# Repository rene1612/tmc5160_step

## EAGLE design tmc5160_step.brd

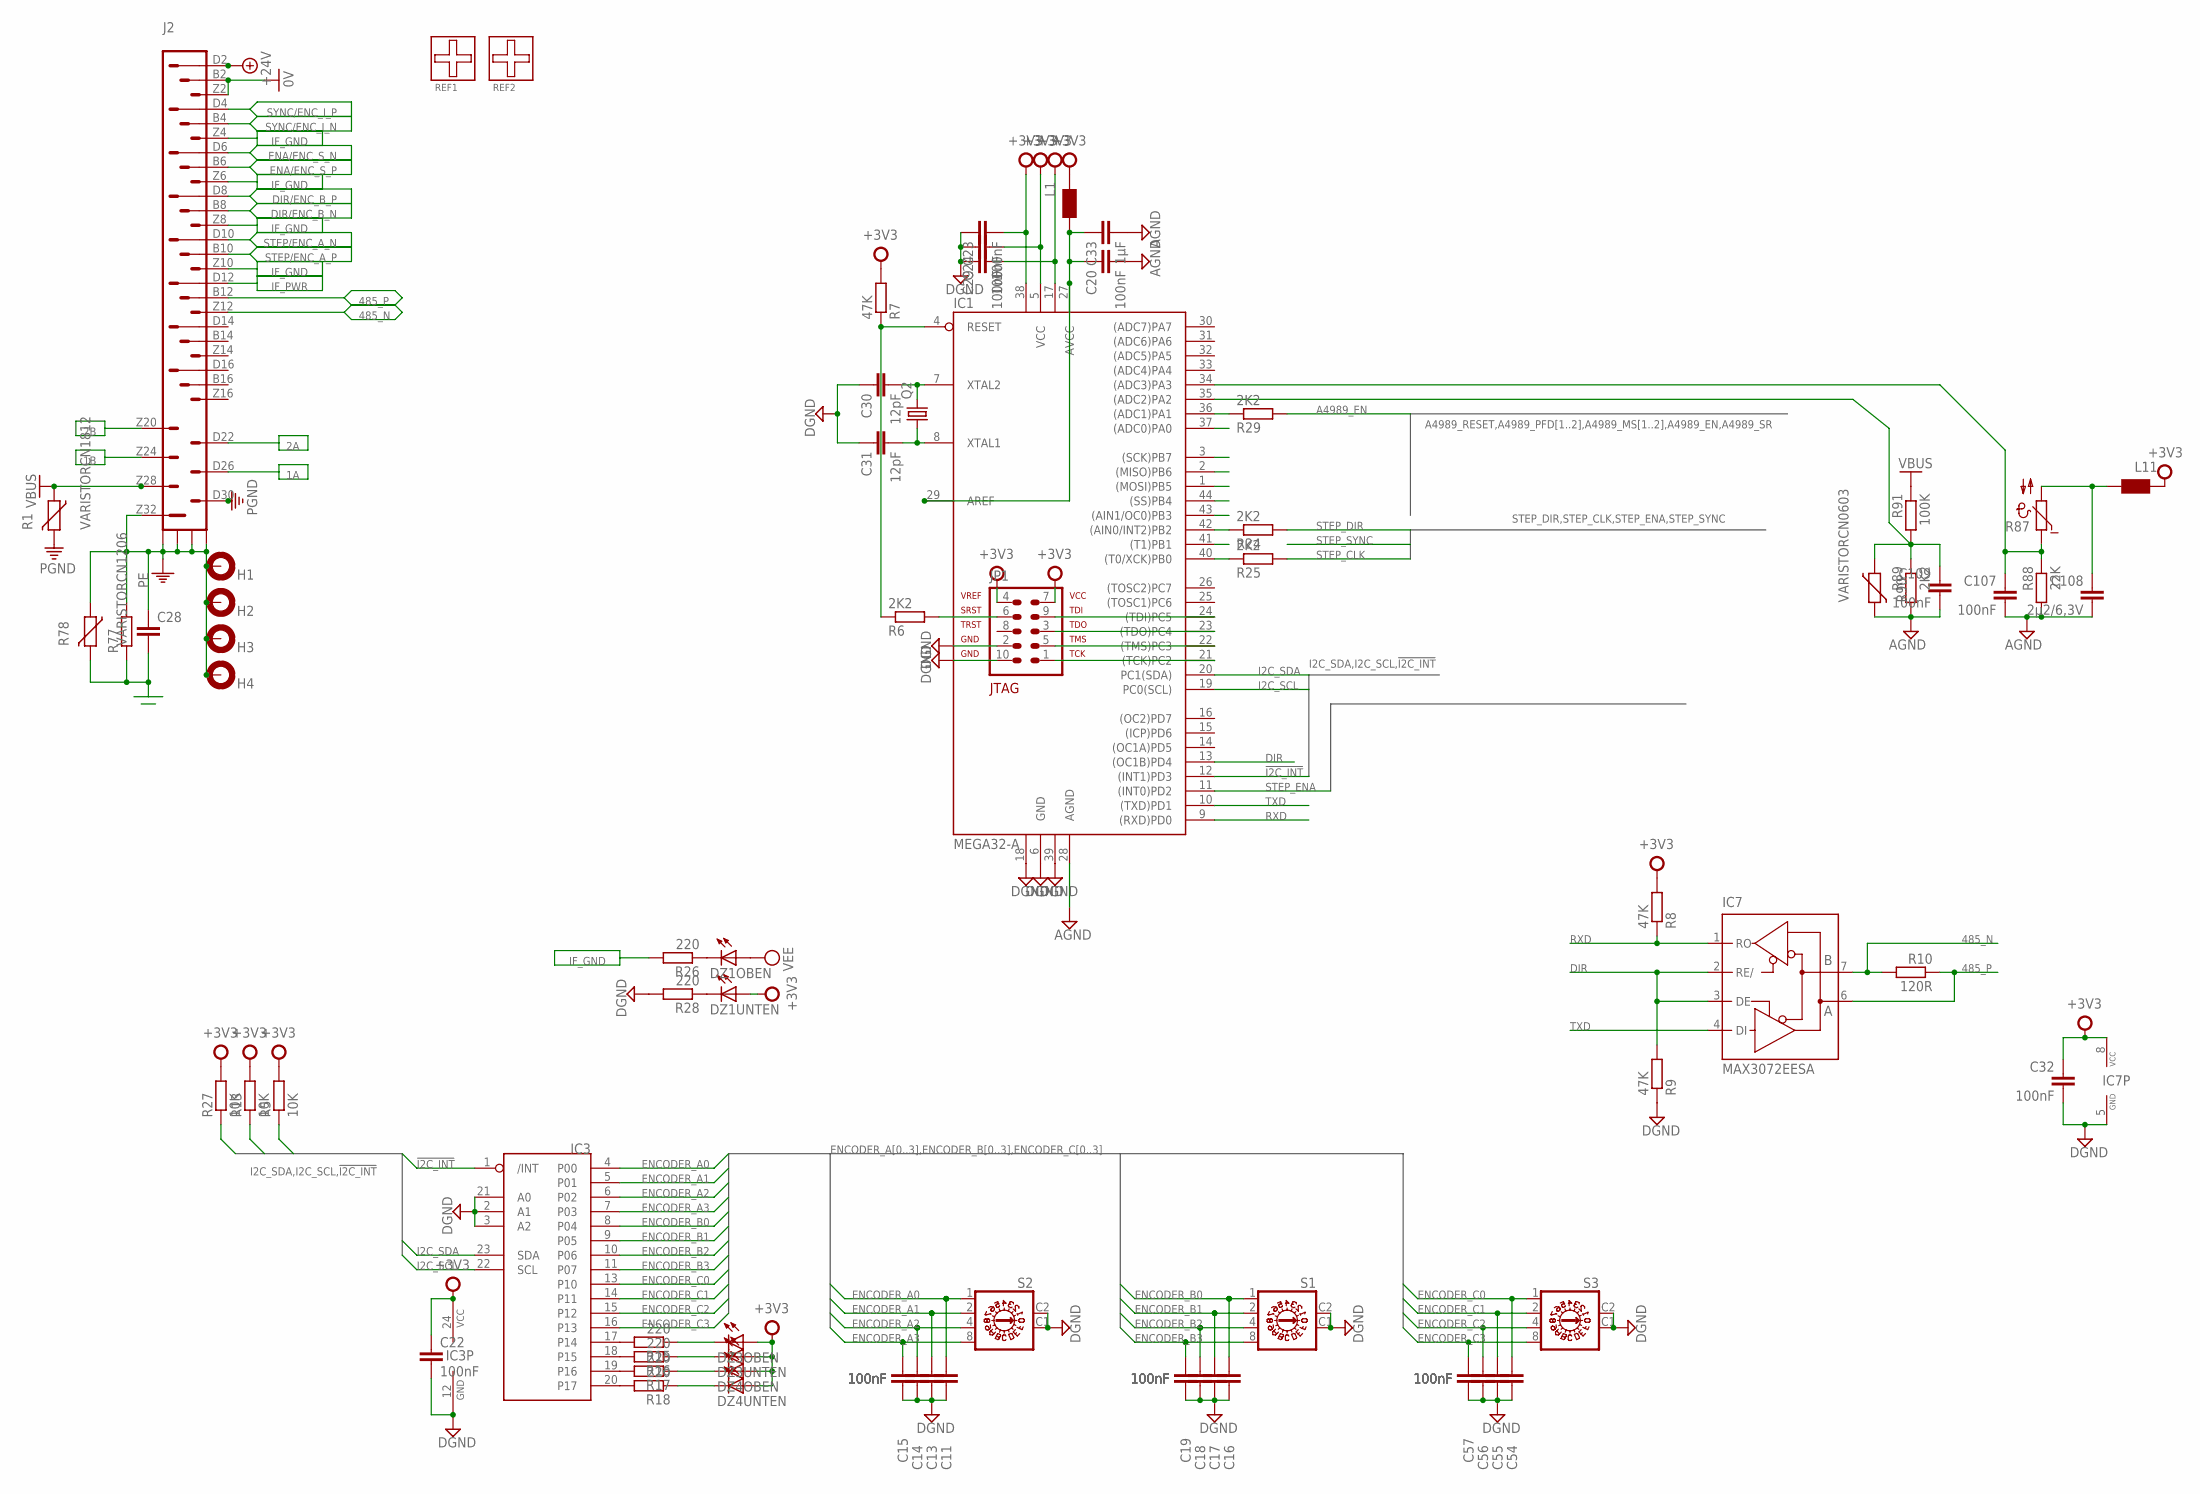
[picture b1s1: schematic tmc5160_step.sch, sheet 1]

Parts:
C11, C13, C14, C15, C16, C17, C18, C19, C20, C22, C23, C24, C29, C32, C54, C55, C56, C57, C107, C109: 100nF; C0603
C28: C-EUC1812; C1812
C30, C31: 12pF; C0603
C33: 1µF; C0603
C108: 2µ2/6,3V; C0603
DZ1, DZ3, DZ4: 18011801; 1801
H1, H2, H3, H4: MOUNT-PAD-ROUND2,5; 2,5-PAD
IC1: MEGA32-A; TQFP44
IC3: PCF8575; MSSOP24
IC7: MAX3072EESA; SO08
J2: H7/24L; H7/24L_EK_FP
JP1: AVR-JTAG-10-R; AVR-JTAG-10R
L1, L11: WE-CBF_0805; 0805
Q2: CRYSTALHC49S; HC49/S
R1: VARISTORCN1812; CT/CN1812
R5, R13, R27: 10K; R0603
R6, R24, R25, R29, R89: 2K2; R0603
R7, R8, R9: 47K; R0603
R10: 120R; R0603
R15, R16, R17, R18, R26, R28: 220; R0603
R77: R-EU_R1206; R1206
R78: VARISTORCN1206; CT/CN1206
R87: NTC642-6; P642
R88: 22K; R0603
R90: VARISTORCN0603; CT/CN0603
R91: 100K; R0603
REF1, REF2: FIDUCIAL_REF-DRUCK; REF-DRUCK
S1, S2, S3: COPAL_HEX

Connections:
0V: J2.B2, J2.Z2; also elsewhere on the board
1A: J2.D26; also elsewhere on the board
1B: J2.Z24; also elsewhere on the board
2A: J2.D22; also elsewhere on the board
2B: J2.Z20; also elsewhere on the board
485_N: IC7.7 (B), J2.Z12, R10.2
485_P: IC7.6 (A), J2.B12, R10.1
!I2C_INT: IC1.12 ((INT1)PD3), IC3.1 (/INT), R5.1
+3V3: C22.1, C23.2, C24.2, C29.2, C32.1, DZ1.UA (A), DZ3.OA (A), DZ3.UA (A), DZ4.OA (A), DZ4.UA (A), IC1.5 (VCC), IC1.17 (VCC1), IC1.38 (VCC2), IC3.24 (VCC), IC7.8 (VCC), JP1.4, JP1.7, L1.1, L11.1, R5.2, R7.2, R8.2, R13.2, R27.2; also elsewhere on the board
+24V: J2.D2; also elsewhere on the board
A4989_EN: R29.2; also elsewhere on the board
AGND: C20.2, C33.2, C107.2, C108.2, C109.2, IC1.28 (AGND), R88.2, R89.2, R90.2; also elsewhere on the board
DGND: C11.1, C13.1, C14.1, C15.1, C16.1, C17.1, C18.1, C19.1, C22.2, C23.1, C24.1, C29.1, C30.1, C31.1, C32.2, C54.1, C55.1, C56.1, C57.1, IC1.6 (GND), IC1.18 (GND1), IC1.39 (GND2), IC3.2 (A1), IC3.3 (A2), IC3.12 (GND), IC3.21 (A0), IC7.5 (GND), JP1.2, JP1.10, R9.1, R28.2, S1.C1, S1.C2, S2.C1, S2.C2, S3.C1, S3.C2; also elsewhere on the board
DIR: IC1.13 ((OC1B)PD4), IC7.2 (RE/), IC7.3 (DE), R9.2
DIR/ENC_B_N: J2.B8; also elsewhere on the board
DIR/ENC_B_P: J2.D8; also elsewhere on the board
ENA/ENC_S_N: J2.D6; also elsewhere on the board
ENA/ENC_S_P: J2.B6; also elsewhere on the board
ENCODER_A0: C11.2, IC3.4 (P00), S2.1
ENCODER_A1: C13.2, IC3.5 (P01), S2.2
ENCODER_A2: C14.2, IC3.6 (P02), S2.4
ENCODER_A3: C15.2, IC3.7 (P03), S2.8
ENCODER_B0: C16.2, IC3.8 (P04), S1.1
ENCODER_B1: C17.2, IC3.9 (P05), S1.2
ENCODER_B2: C18.2, IC3.10 (P06), S1.4
ENCODER_B3: C19.2, IC3.11 (P07), S1.8
ENCODER_C0: C54.2, IC3.13 (P10), S3.1
ENCODER_C1: C55.2, IC3.14 (P11), S3.2
ENCODER_C2: C56.2, IC3.15 (P12), S3.4
ENCODER_C3: C57.2, IC3.16 (P13), S3.8
I2C_SCL: IC1.19 (PC0(SCL)), IC3.22 (SCL), R27.1
I2C_SDA: IC1.20 (PC1(SDA)), IC3.23 (SDA), R13.1
IF_GND: J2.Z4, J2.Z6, J2.Z8, J2.Z10, R26.2; also elsewhere on the board
IF_PWR: J2.D12; also elsewhere on the board
unnamed: JP1.6, R6.2
unnamed: IC1.4 (RESET), R6.1, R7.1
unnamed: C107.1, IC1.34 ((ADC3)PA3), R87.1, R88.1
unnamed: IC1.21 ((TCK)PC2), JP1.1
unnamed: IC1.22 ((TMS)PC3), JP1.5
unnamed: IC1.23 ((TDO)PC4), JP1.3
unnamed: IC1.24 ((TDI)PC5), JP1.9
unnamed: C20.1, C33.1, IC1.27 (AVCC), IC1.29 (AREF), L1.2
unnamed: C30.2, IC1.7 (XTAL2), Q2.2
unnamed: C31.2, IC1.8 (XTAL1), Q2.1
unnamed: DZ3.OK (C), R15.1
unnamed: DZ3.UK (C), R16.1
unnamed: DZ4.OK (C), R17.1
unnamed: DZ4.UK (C), R18.1
unnamed: IC3.17 (P14), R15.2
unnamed: IC3.18 (P15), R16.2
unnamed: IC3.19 (P16), R17.2
unnamed: IC3.20 (P17), R18.2
unnamed: IC1.42 ((AIN0/INT2)PB2), R24.1
unnamed: IC1.40 ((T0/XCK)PB0), R25.1
unnamed: DZ1.OK (C), R26.1
unnamed: DZ1.UK (C), R28.1
unnamed: IC1.36 ((ADC1)PA1), R29.1
unnamed: C108.1, L11.2, R87.2
unnamed: C109.1, IC1.35 ((ADC2)PA2), R89.1, R90.1, R91.2
PE: C28.1, H1.B2,5, H2.B2,5, H3.B2,5, H4.B2,5, J2.S1, J2.S2, J2.S3, J2.S4, J2.Z32, R77.2, R78.1; also elsewhere on the board
PGND: J2.D30, R1.2; also elsewhere on the board
RXD: IC1.9 ((RXD)PD0), IC7.1 (RO), R8.1
SGND: C28.2, R77.1, R78.2; also elsewhere on the board
STEP/ENC_A_N: J2.D10; also elsewhere on the board
STEP/ENC_A_P: J2.B10; also elsewhere on the board
STEP_CLK: R25.2; also elsewhere on the board
STEP_DIR: R24.2; also elsewhere on the board
STEP_ENA: IC1.11 ((INT0)PD2); also elsewhere on the board
SYNC/ENC_I_N: J2.B4; also elsewhere on the board
SYNC/ENC_I_P: J2.D4; also elsewhere on the board
TXD: IC1.10 ((TXD)PD1), IC7.4 (DI)
VBUS: J2.Z28, R1.1, R91.1; also elsewhere on the board
VEE: DZ1.OA (A); also elsewhere on the board

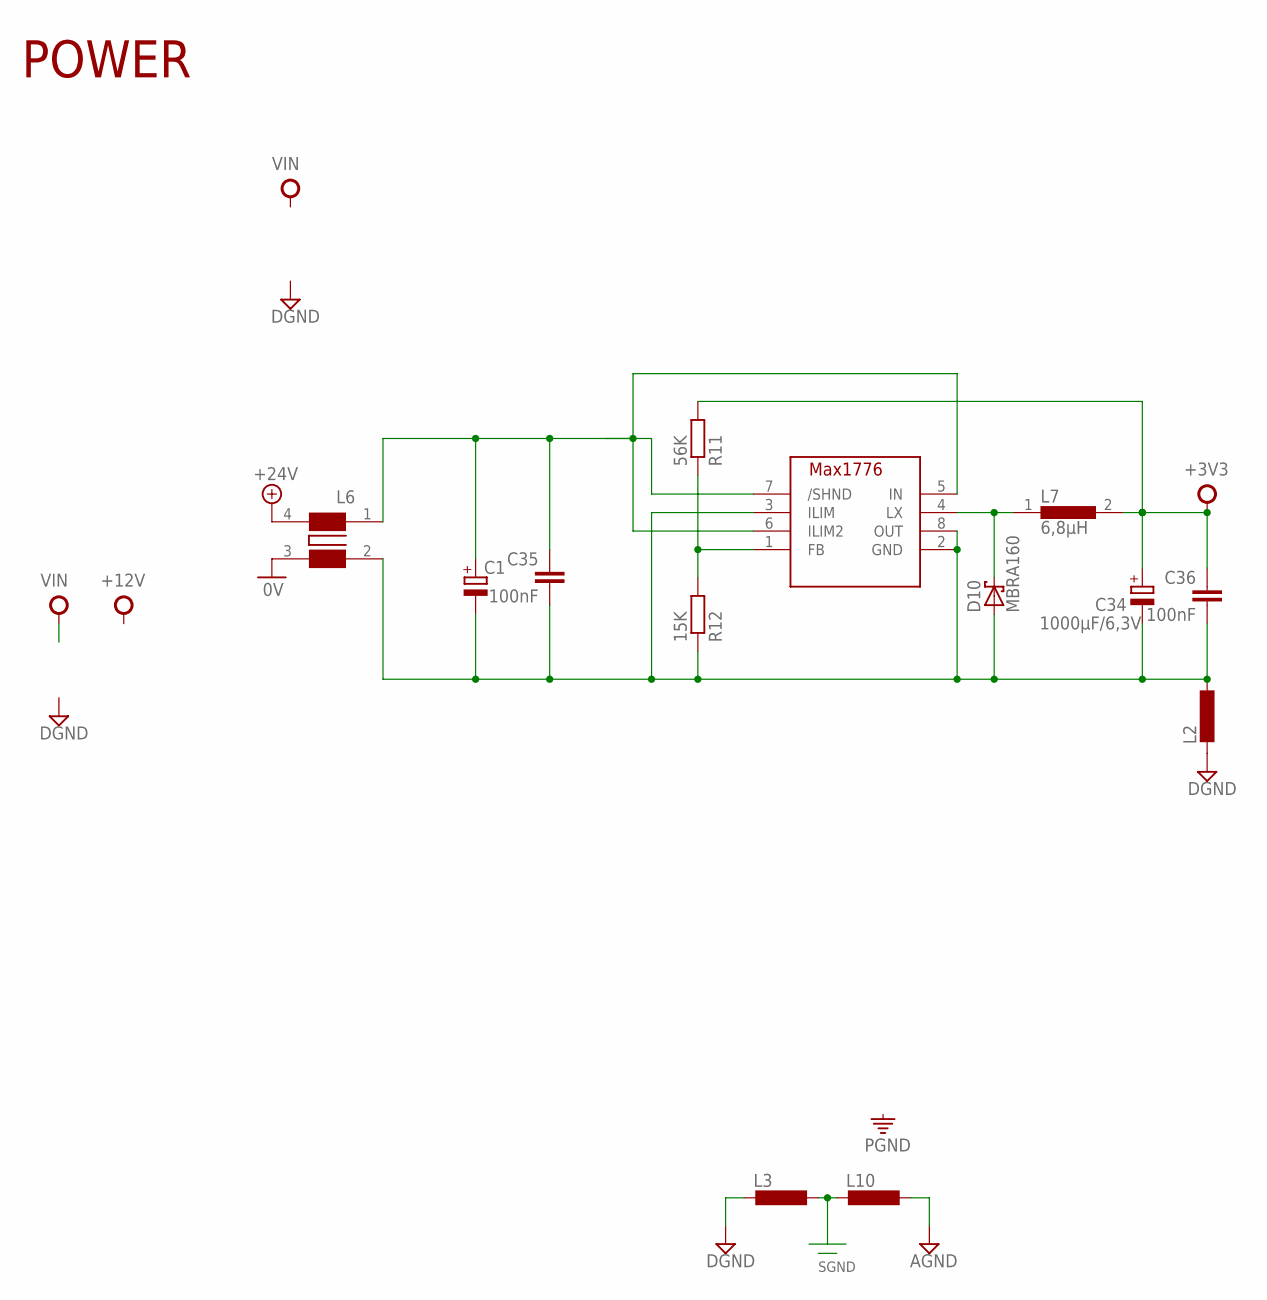
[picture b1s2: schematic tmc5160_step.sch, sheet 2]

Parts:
C1: CPOL-EUE3.5-8; E3,5-8
C34: 1000µF/6,3V; E3,5-8
C35, C36: 100nF; C0603
D10: MBRA160; SMB
IC8: MAX1776; UMAX8
L2, L3, L10: L-EUL2825P; L2825P
L6: WE-CMS; WE-CMS_7427521
L7: 6,8µH; B82472
R11: 56K; R0603
R12: 15K; R0603

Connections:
0V: L6.3 (2); also elsewhere on the board
+3V3: C34.+, C36.1, L7.2, R11.2; also elsewhere on the board
+24V: L6.4; also elsewhere on the board
AGND: L10.1; also elsewhere on the board
DGND: L2.2, L3.2; also elsewhere on the board
unnamed: D10.C, IC8.4 (LX), L7.1
unnamed: IC8.1 (FB), R11.1, R12.2
unnamed: C1.+, C35.1, IC8.5 (IN), IC8.6 (ILIM2), IC8.7 (/SHND), L6.1 (3)
unnamed: C1.-, C34.-, C35.2, C36.2, D10.A, IC8.2 (GND), IC8.3 (ILIM), IC8.8 (OUT), L2.1, L6.2 (1), R12.1
SGND: L3.1, L10.2; also elsewhere on the board

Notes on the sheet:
POWER

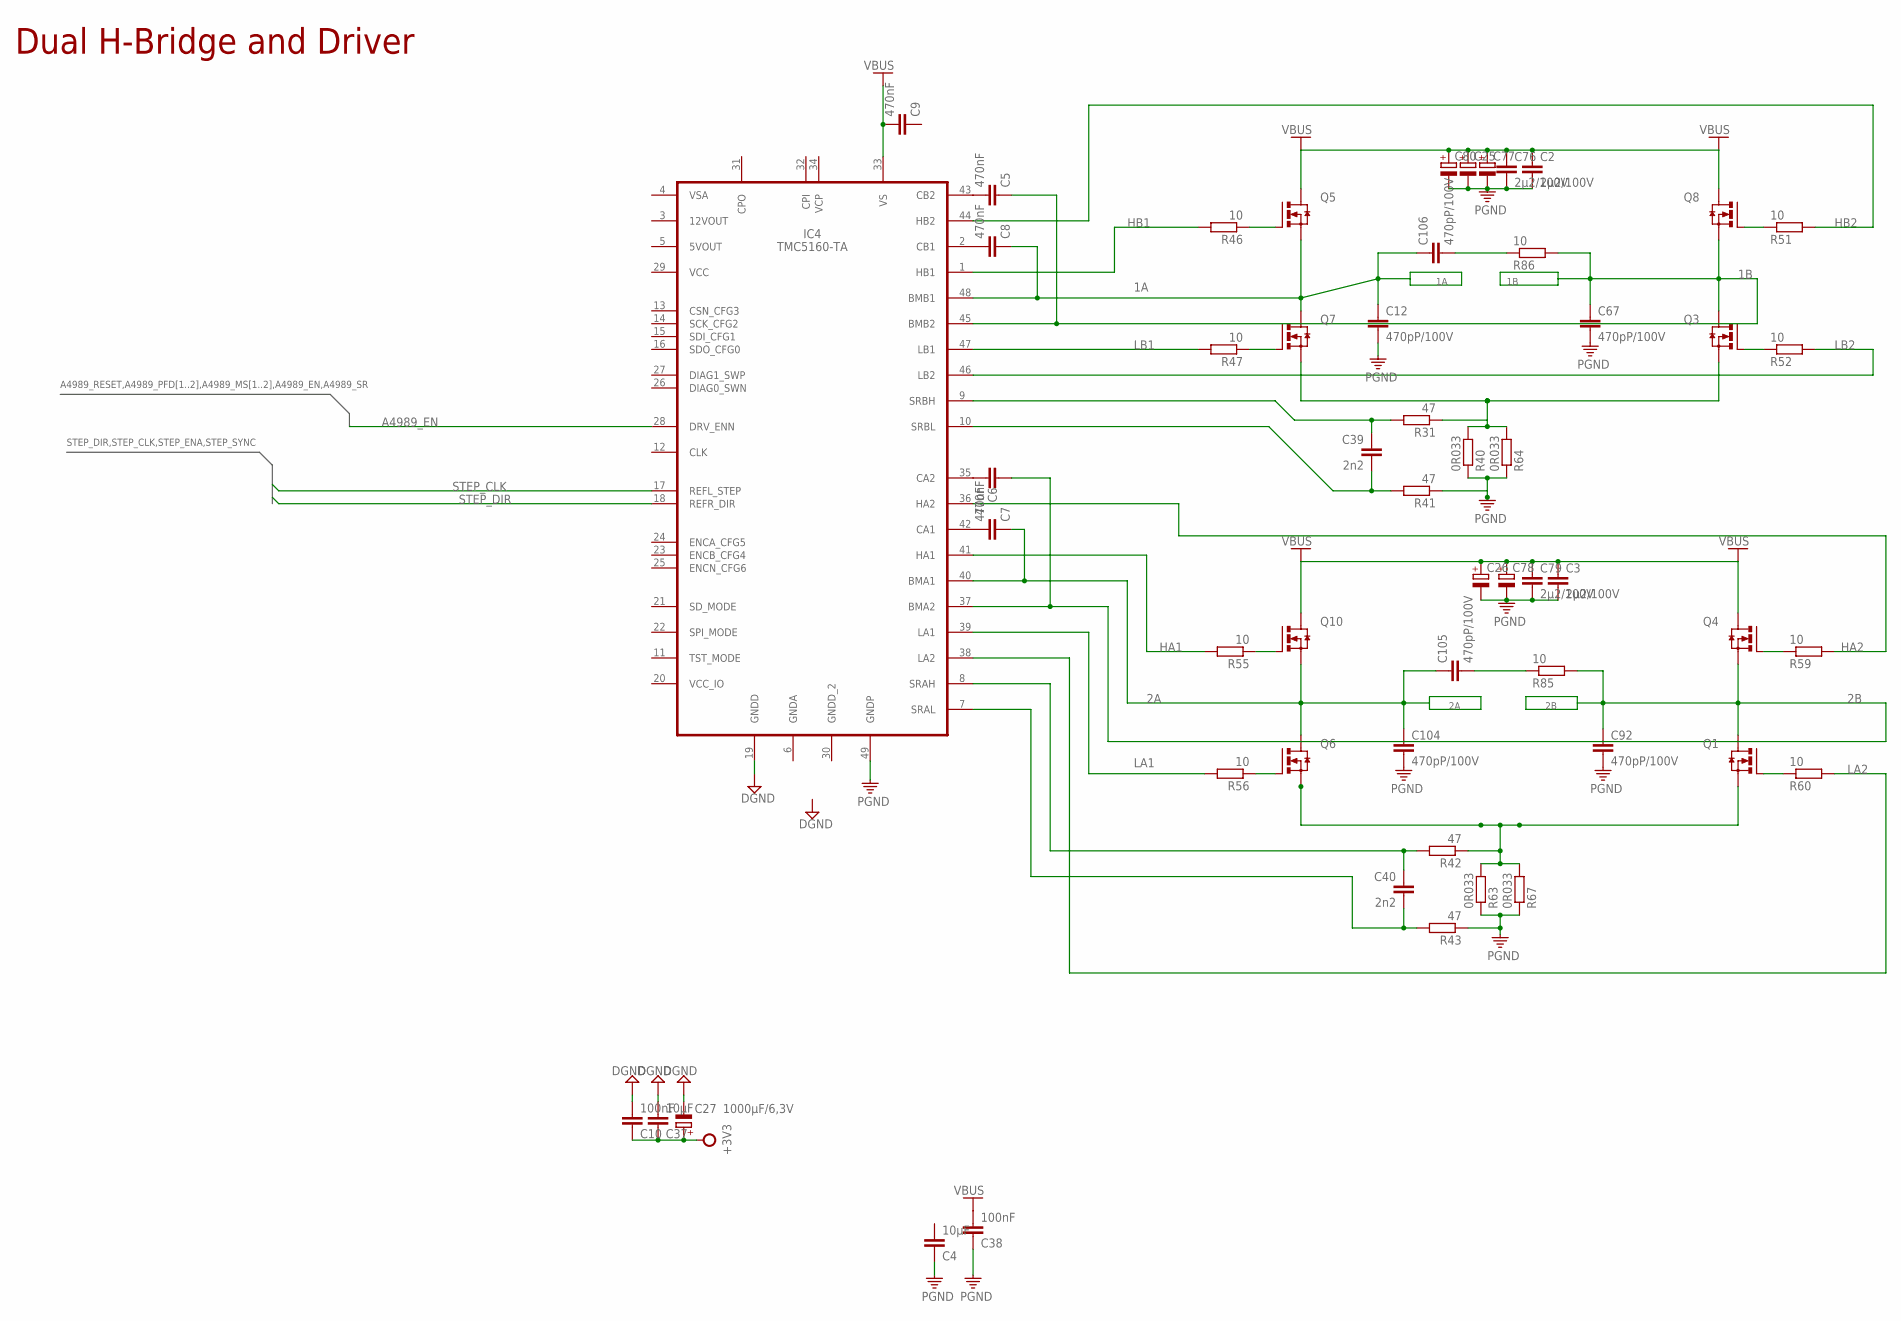
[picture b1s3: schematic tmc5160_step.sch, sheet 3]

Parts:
C2, C3, C76, C79: 2µ2/100V; C1812
C4: 10µF; C1206
C5, C6, C7, C8, C9: 470nF; C0603
C10, C38: 100nF; C0603
C12, C67, C92, C104, C105, C106: 470pP/100V; C1210
C25, C26, C77, C78, C80: CPOL-EUE5-10.5; E5-10,5
C27: 1000µF/6,3V; E2,5-6
C37: 10µF; C0805
C39, C40: 2n2; C0603
IC4: TMC5160-TA; TQFP48-EP
Q1, Q3, Q4, Q5, Q6, Q7, Q8, Q10: SUD40N10; D-PAK_TO252AA
R31, R41, R42, R43: 47; R0603
R40, R63, R64, R67: 0R033; R2512
R46, R47, R51, R52, R55, R56, R59, R60: 10; R0603
R85, R86: 10; R1206

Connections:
1A: C8.1, C12.1, C106.1, IC4.48 (BMB1), Q5.3 (S), Q7.4 (D); also elsewhere on the board
1B: C5.1, C67.1, IC4.45 (BMB2), Q3.4 (D), Q8.3 (S), R86.2; also elsewhere on the board
2A: C7.1, C104.1, C105.1, IC4.40 (BMA1), Q6.4 (D), Q10.3 (S); also elsewhere on the board
2B: C6.1, C92.1, IC4.37 (BMA2), Q1.4 (D), Q4.3 (S), R85.2; also elsewhere on the board
+3V3: C10.1, C27.+, C37.1; also elsewhere on the board
A4989_EN: IC4.28 (DRV_ENN); also elsewhere on the board
DGND: C10.2, C27.-, C37.2, IC4.19 (GNDD); also elsewhere on the board
GNDA: IC4.6 (GNDA)
GNDD_2: IC4.30 (GNDD_2)
HA1: IC4.41 (HA1), R55.2
HA2: IC4.36 (HA2), R59.2
HB1: IC4.1 (HB1), R46.2
HB2: IC4.44 (HB2), R51.2
LA1: IC4.39 (LA1), R56.2
LA2: IC4.38 (LA2), R60.2
LB1: IC4.47 (LB1), R47.2
LB2: IC4.46 (LB2), R52.2
unnamed: C5.2, IC4.43 (CB2)
unnamed: C39.1, IC4.9 (SRBH), R31.2
unnamed: C39.2, IC4.10 (SRBL), R41.2
unnamed: C8.2, IC4.2 (CB1)
unnamed: C7.2, IC4.42 (CA1)
unnamed: C6.2, IC4.35 (CA2)
unnamed: C40.1, IC4.8 (SRAH), R42.2
unnamed: C40.2, IC4.7 (SRAL), R43.2
unnamed: Q5.1 (G), R46.1
unnamed: Q7.1 (G), R47.1
unnamed: Q3.1 (G), R52.1
unnamed: Q8.1 (G), R51.1
unnamed: Q10.1 (G), R55.1
unnamed: Q6.1 (G), R56.1
unnamed: Q1.1 (G), R60.1
unnamed: Q4.1 (G), R59.1
unnamed: C105.2, R85.1
unnamed: C106.2, R86.1
PGND: C2.2, C3.2, C4.1, C12.2, C25.-, C26.-, C38.1, C67.2, C76.2, C77.-, C78.-, C79.2, C80.-, C92.2, C104.2, IC4.49 (GNDP), R40.1, R41.1, R43.1, R63.1, R64.1, R67.1; also elsewhere on the board
SENSE1: Q3.3 (S), Q7.3 (S), R31.1, R40.2, R64.2
SENSE2: Q1.3 (S), Q6.3 (S), R42.1, R63.2, R67.2
STEP_CLK: IC4.17 (REFL_STEP); also elsewhere on the board
STEP_DIR: IC4.18 (REFR_DIR); also elsewhere on the board
VBUS: C2.1, C3.1, C9.2, C25.+, C26.+, C38.2, C76.1, C77.+, C78.+, C79.1, C80.+, IC4.33 (VS), Q4.4 (D), Q5.4 (D), Q8.4 (D), Q10.4 (D); also elsewhere on the board
VCC: IC4.29 (VCC)
VCC_IO: IC4.20 (VCC_IO)
VSA: IC4.4 (VSA)

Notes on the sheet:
Dual H-Bridge and Driver

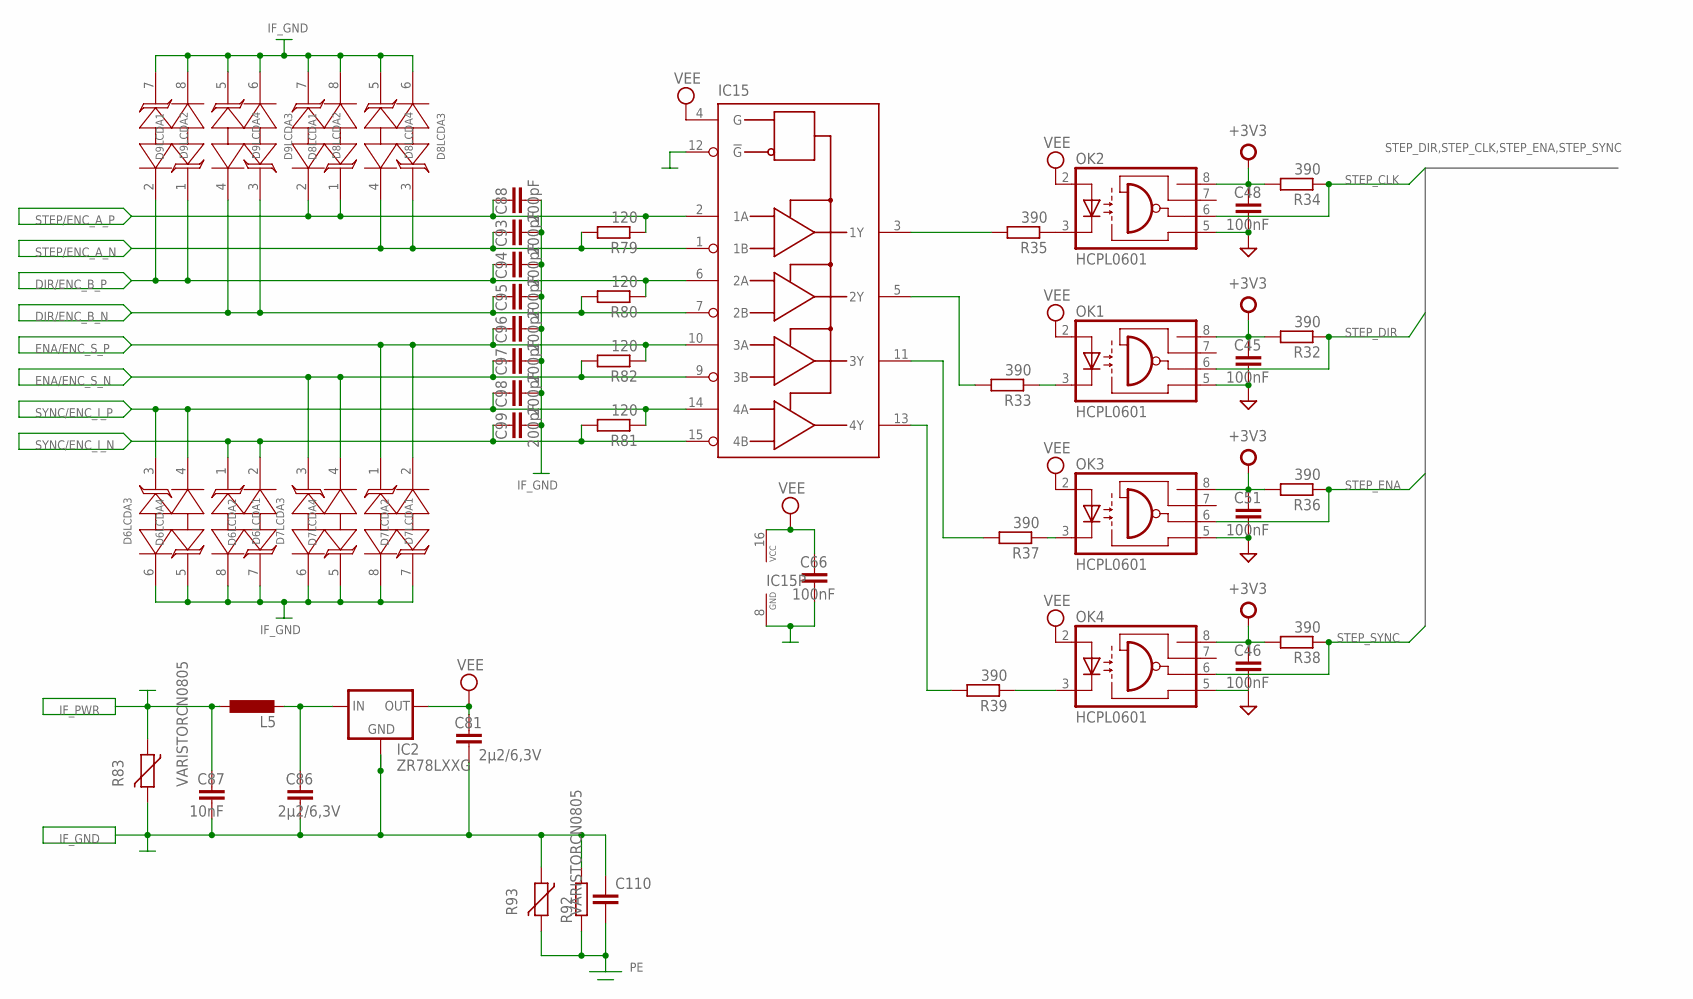
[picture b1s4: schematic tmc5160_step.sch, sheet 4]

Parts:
C45, C46, C48, C51, C66: 100nF; C0603
C81: 2µ2/6,3V; C1210
C86: 2µ2/6,3V; C0603
C87: 10nF; C0603
C88, C93, C94, C95, C96, C97, C98, C99: 200pF; C0603
C110: C-EUC1206; C1206
D6, D7, D8, D9: LCDAXXSO08; SO08
IC2: ZR78LXXG; SO223G
IC15: AM26LV32; SO-16
L5: L-EUL2825P; L2825P
OK1, OK2, OK3, OK4: HCPL0601; SOIC08
R32, R33, R34, R35, R36, R37, R38, R39: 390; R0603
R79, R80, R81, R82: 120; R0603
R83, R93: VARISTORCN0805; CT/CN0805
R92: R-EU_R1206; R1206

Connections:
+3V3: C45.1, C46.1, C48.1, C51.1, OK1.8 (VCC), OK2.8 (VCC), OK3.8 (VCC), OK4.8 (VCC), R32.2, R34.2, R36.2, R38.2; also elsewhere on the board
DGND: C45.2, C46.2, C48.2, C51.2, OK1.5 (GND), OK2.5 (GND), OK3.5 (GND), OK4.5 (GND); also elsewhere on the board
DIR/ENC_B_N: C95.1, D9.3 (1), D9.4 (2), IC15.7 (2B), R80.2; also elsewhere on the board
DIR/ENC_B_P: C94.1, D9.1, D9.2, IC15.6 (2A), R80.1; also elsewhere on the board
ENA/ENC_S_N: C97.1, D7.3 (1), D7.4 (2), IC15.9 (3B), R82.2; also elsewhere on the board
ENA/ENC_S_P: C96.1, D7.1, D7.2, IC15.10 (3A), R82.1; also elsewhere on the board
IF_GND: C66.2, C81.2, C86.2, C87.2, C88.2, C93.2, C94.2, C95.2, C96.2, C97.2, C98.2, C99.2, C110.1, D6.5 (1), D6.6 (2), D6.7 (1), D6.8 (2), D7.5 (1), D7.6 (2), D7.7 (1), D7.8 (2), D8.5 (1), D8.6 (2), D8.7 (1), D8.8 (2), D9.5 (1), D9.6 (2), D9.7 (1), D9.8 (2), IC2.2 (GND), IC2.4 (GND1), IC15.8 (GND), IC15.12 (!G), R83.2, R92.2, R93.1; also elsewhere on the board
IF_PWR: C87.1, L5.1, R83.1; also elsewhere on the board
IN_DIR/ENC_B: IC15.5 (2Y), R33.2
IN_ENA/ENC_S: IC15.11 (3Y), R37.2
IN_STEP/ENC_A: IC15.3 (1Y), R35.2
IN_SYNC/ENC_I: IC15.13 (4Y), R39.2
unnamed: C86.1, IC2.3 (IN), L5.2
unnamed: OK1.3 (C), R33.1
unnamed: OK4.3 (C), R39.1
unnamed: OK2.3 (C), R35.1
unnamed: OK3.3 (C), R37.1
PE: C110.2, R92.1, R93.2; also elsewhere on the board
STEP/ENC_A_N: C93.1, D8.3 (1), D8.4 (2), IC15.1 (1B), R79.2; also elsewhere on the board
STEP/ENC_A_P: C88.1, D8.1, D8.2, IC15.2 (1A), R79.1; also elsewhere on the board
STEP_CLK: OK2.6 (VO), R34.1; also elsewhere on the board
STEP_DIR: OK1.6 (VO), R32.1; also elsewhere on the board
STEP_ENA: OK3.6 (VO), R36.1; also elsewhere on the board
STEP_SYNC: OK4.6 (VO), R38.1
SYNC/ENC_I_N: C99.1, D6.1, D6.2, IC15.15 (4B), R81.2; also elsewhere on the board
SYNC/ENC_I_P: C98.1, D6.3 (1), D6.4 (2), IC15.14 (4A), R81.1; also elsewhere on the board
VEE: C66.1, C81.1, IC2.1 (OUT), IC15.4 (G), IC15.16 (VCC), OK1.2 (A), OK2.2 (A), OK3.2 (A), OK4.2 (A); also elsewhere on the board

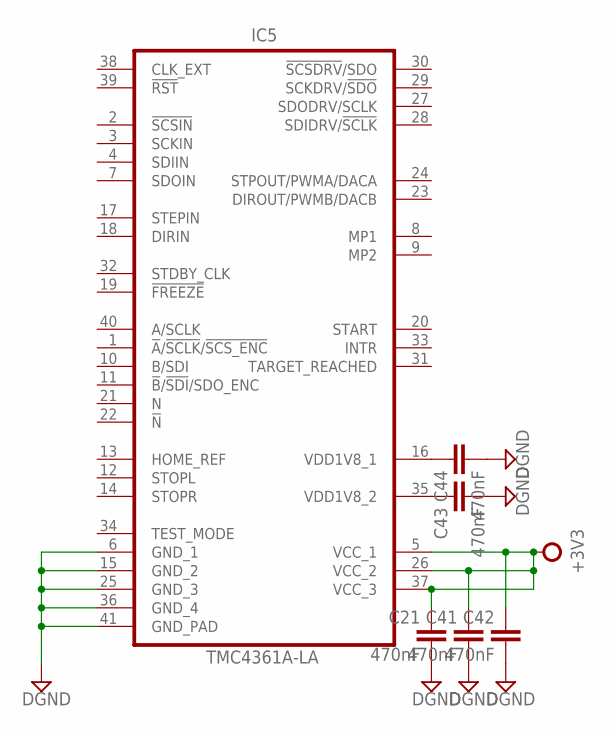
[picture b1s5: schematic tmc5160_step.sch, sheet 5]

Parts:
C21, C41, C42, C43, C44: 470nF; C0603
IC5: TMC4361A-LA; TMC_QFN40_0.5_6.0X6.0

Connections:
+3V3: C21.1, C41.1, C42.1, IC5.5 (VCC_1), IC5.26 (VCC_2), IC5.37 (VCC_3); also elsewhere on the board
DGND: C21.2, C41.2, C42.2, C43.2, C44.2, IC5.6 (GND_1), IC5.15 (GND_2), IC5.25 (GND_3), IC5.36 (GND_4), IC5.41 (GND_PAD); also elsewhere on the board
unnamed: C43.1, IC5.35 (VDD1V8_2)
unnamed: C44.1, IC5.16 (VDD1V8_1)

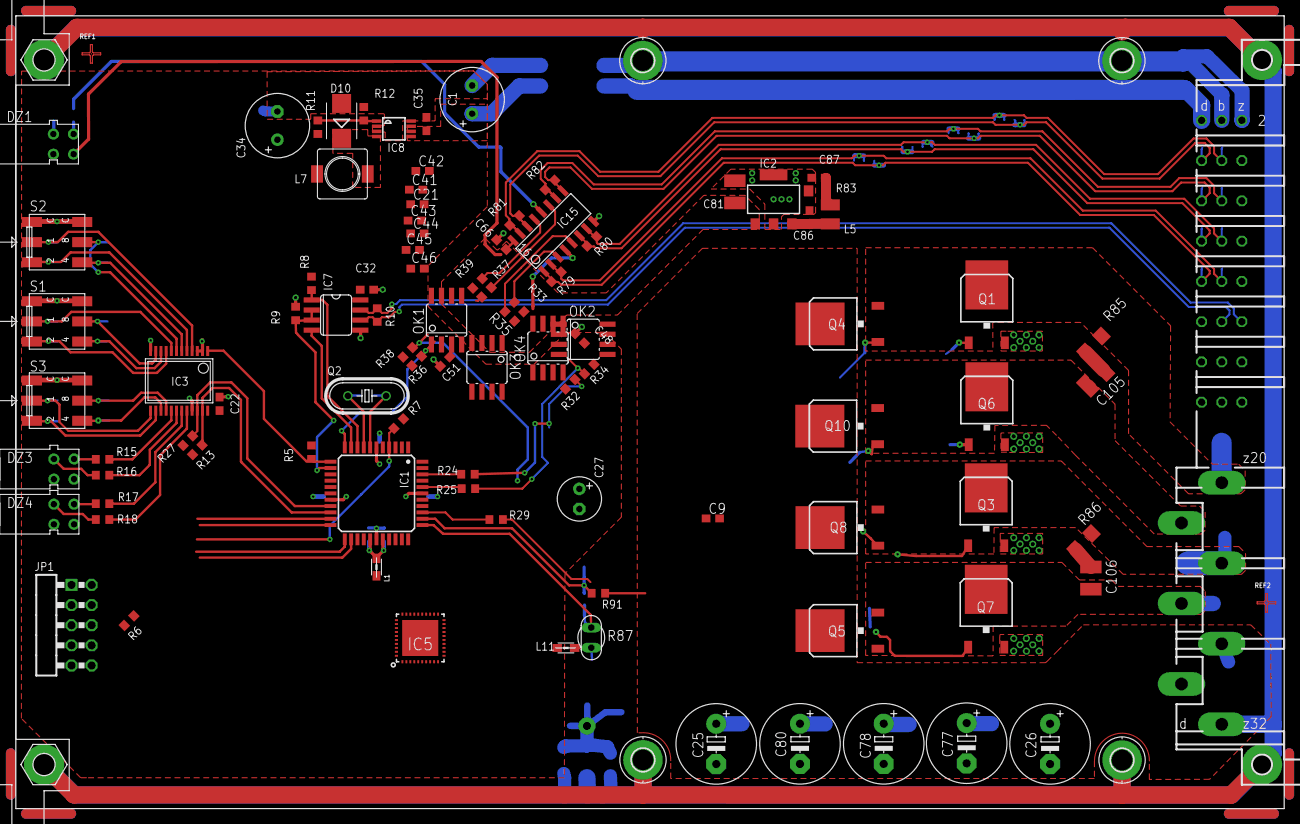
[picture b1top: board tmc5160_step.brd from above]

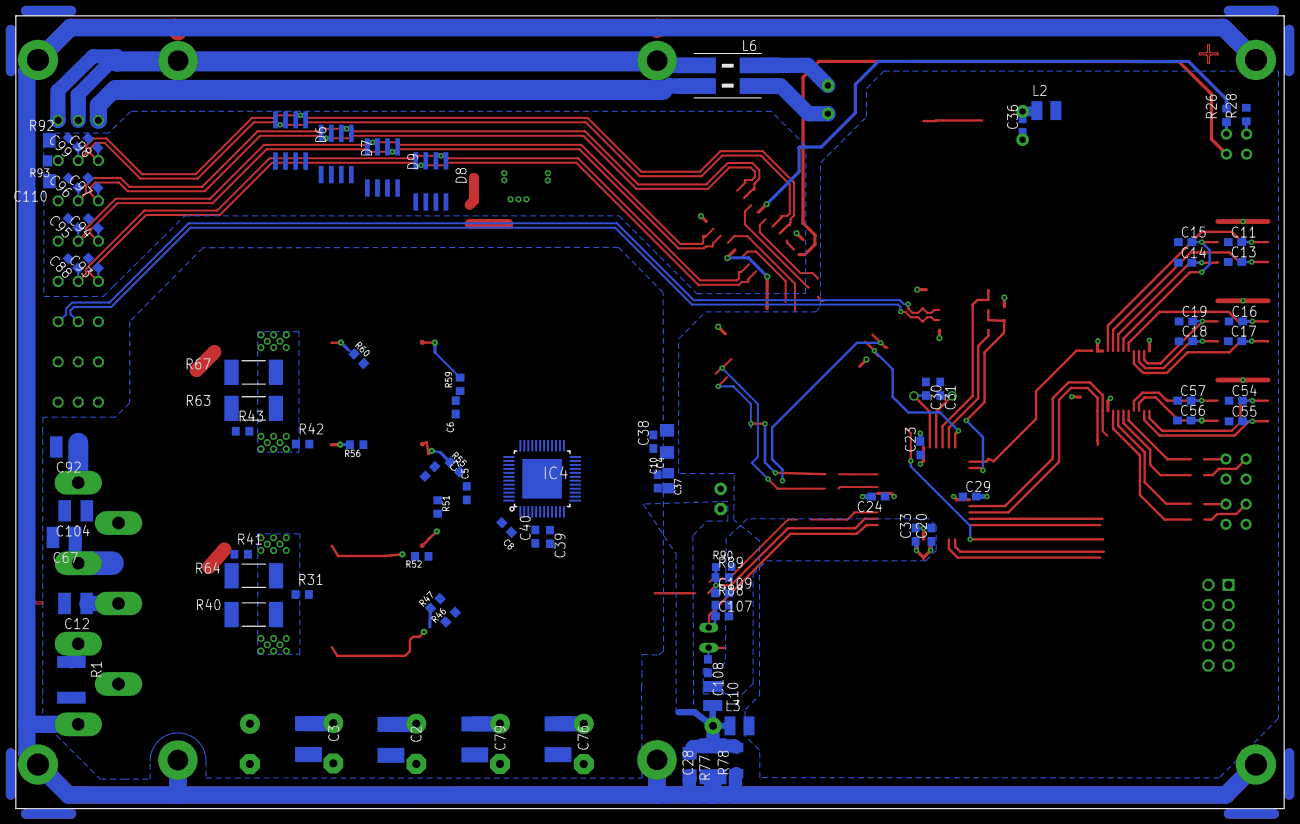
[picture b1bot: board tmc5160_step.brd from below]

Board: 2 copper layers, 160.0 x 100.0 mm, 186 parts (86 on the bottom side), 117 nets.

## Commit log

2018-08-31 erstes commit, fork von A4989_step
2018-09-07 tmc4361 hinzugefügt

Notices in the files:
parts and their libraries:
wuerth_elektronik_v5: Copyright: Würth Elektronik eiSos
